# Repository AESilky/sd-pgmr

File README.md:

# Silky Design - Flash ROM Programmer

This is a programmer for the popular SST39SF010A/020A/040 devices from MicroChip.

These devices are 128Mx8, 256Mx8, and 512Mx8, and are used in a number of retro-computing memory and single-board-computers.

The programmer uses a Raspberry Pi Pico2 (RP2350) micro-controller to read image files from a MicroSD card or from the USB port from an application running on a host computer. The RPi Pico2 buffers the image in its internal memory and then writes it to the device.

The programmer can read a Flash device and provides options of saving the device image to the SD card, sending it to a host computer, or writing the image onto another Flash device.

The programmer is powered from the USB port on the RPi Pico2.

The programmer includes a small display and an input knob and switch to navigate through the options, SD card contents, etc.

## Repo Contents

This repo includes:

1. the hardware schematic, PCB layout, and other files needed to produce the PCB.
2. the software for the RPi Pico2, including CMake files to build the RPi Pico2 image.
3. some software for a host computer to communicate with the programmer and transfer files.
4. some component data sheets (for the more unique components)
5. 3D print files for a simple enclosure

## License

Except where noted, the software and hardware for this project is designed/authored by AESilky, and is licensed under the MIT License (included in the repo in the LICENSE file).

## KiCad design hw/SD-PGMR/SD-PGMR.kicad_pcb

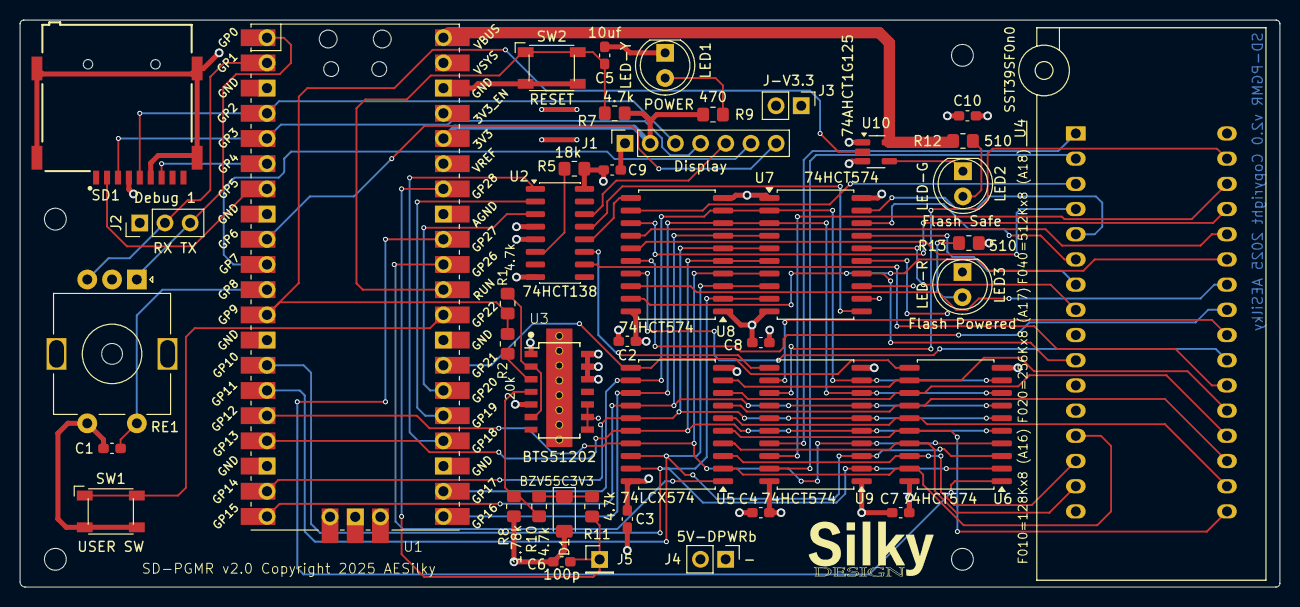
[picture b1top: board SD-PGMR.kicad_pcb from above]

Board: 4 copper layers, 127.0 x 57.1 mm, 48 parts (0 on the bottom side), 75 nets.

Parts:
C1, C2, C3, C4, C7, C8, C9, C10: 0.1uF; C_0603_1608Metric_Pad1.08x0.95mm_HandSolder
C5: 10uf; C_0603_1608Metric_Pad1.08x0.95mm_HandSolder
C6: 100p; C_0603_1608Metric_Pad1.08x0.95mm_HandSolder
D1: BZV55C3V3; D_MiniMELF
G1: LOGO; SILKY-DESIGN-logo-0_50-AES
H1, H2, H3, H4: MountingHole; MountingHole_2.2mm_M2
J1: CONN_01x07 Socket; PinSocket_1x07_P2.54mm_Vertical
J2: Conn_01x03 HDR; PinHeader_1x03_P2.54mm_Vertical
J3: J-V3.3; PinHeader_1x02_P2.54mm_Vertical
J4: CONN 1x2 HDR; PinHeader_1x02_P2.54mm_Vertical
J5: HDR 1x1 Pin; PinHeader_1x01_P2.54mm_Vertical
LED1: LED-Y; LED_D5.0mm
LED2: LED-G; LED_D5.0mm
LED3: LED-R; LED_D5.0mm
R1, R7, R10, R11: 4.7k; R_0805_2012Metric_Pad1.20x1.40mm_HandSolder
R2: 20k; R_0805_2012Metric_Pad1.20x1.40mm_HandSolder
R5: 18k; R_0805_2012Metric_Pad1.20x1.40mm_HandSolder
R8: 1.78k; R_0805_2012Metric_Pad1.20x1.40mm_HandSolder
R9: 470; R_0805_2012Metric_Pad1.20x1.40mm_HandSolder
R12, R13: 510; R_0805_2012Metric_Pad1.20x1.40mm_HandSolder
RE1: RotEnc-SW; RotaryEncoder_Alps_EC11E-Switch_Vertical_H20mm_MountingHoles
SD1: MicroSD-Socket; AES-SDCard-GCT_MEM2075-00-140-01-A
SW1, SW2: SW PB-MOM; AES-SW_PUSH_SMD_1P1T_NO_45x45mm-CK
U1: AES-Pico; AES-RPi_Pico_SMD_TH
U2: 74HCT138; SOIC-16_3.9x9.9mm_P1.27mm
U3: BTS51202; AES-Inf-BTS5120-DSOP14-BP
U4: SST39SF0n0; DIP_Socket-32_W11.9_W12.7_W15.24_W17.78_W18.5_3M_232-1285-0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
U5: 74LCX574; SOIC-20W_7.5x12.8mm_P1.27mm
U6, U7, U8, U9: 74HCT574; SOIC-20W_7.5x12.8mm_P1.27mm
U10: 74AHCT1G125; SOT-23-5_HandSoldering

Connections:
+3.3V: C3.2, J1.2, J3.2, R7.1, R9.1, SD1.4 (VDD), U1.36 (3V3), U5.20 (VCC)
+5DP: C2.2, C4.2, C7.2, C8.2, C9.2, C10.2, R5.2, R13.2, U2.16 (VCC), U3.12 (OUT0a), U3.13 (OUT0b), U3.14 (OUT0c), U4.32 (VCC), U6.20 (VCC), U7.20 (VCC), U8.20 (VCC), U9.20 (VCC)
+5V: R12.1, U1.39 (VSYS), U1.40 (VBUS), U3.CT (VS), U10.5 (VCC)
/A0: U1.24 (GPIO18), U2.1 (A0)
/A1: U1.25 (GPIO19), U2.2 (A1)
/A2: U1.26 (GPIO20), U2.3 (A2)
/ADH_LD-: U2.11 (O4), U9.11 (Cp)
/ADL_LD-: U2.13 (O2), U7.11 (Cp)
/ADM_LD-: U2.12 (O3), U8.11 (Cp)
/ATTN-: SW1.1, U1.29 (GPIO22)
/BA0: U4.12 (A0), U7.12 (Q7)
/BA1: U4.11 (A1), U7.13 (Q6)
/BA2: U4.10 (A2), U7.14 (Q5)
/BA3: U4.9 (A3), U7.15 (Q4)
/BA4: U4.8 (A4), U7.16 (Q3)
/BA5: U4.7 (A5), U7.17 (Q2)
/BA6: U4.6 (A6), U7.18 (Q1)
/BA7: U4.5 (A7), U7.19 (Q0)
/BA8: U4.27 (A8), U8.19 (Q0)
/BA9: U4.26 (A9), U8.18 (Q1)
/BA10: U4.23 (A10), U8.17 (Q2)
/BA11: U4.25 (A11), U8.16 (Q3)
/BA12: U4.4 (A12), U8.15 (Q4)
/BA13: U4.28 (A13), U8.14 (Q5)
/BA14: U4.29 (A14), U8.13 (Q6)
/BA15: U4.3 (A15), U8.12 (Q7)
/BA16: U4.2 (A16), U9.19 (Q0)
/BA17: U4.30 (A17), U9.18 (Q1)
/BA18: U4.1 (A18), U9.17 (Q2)
/BD0: U4.13 (D0), U5.2 (D0), U6.19 (Q0)
/BD1: U4.14 (D1), U5.3 (D1), U6.18 (Q1)
/BD2: U4.15 (D2), U5.4 (D2), U6.17 (Q2)
/BD3: U4.17 (D3), U5.5 (D3), U6.16 (Q3)
/BD4: U4.18 (D4), U5.6 (D4), U6.15 (Q4)
/BD5: U4.19 (D5), U5.7 (D5), U6.14 (Q5)
/BD6: U4.20 (D6), U5.8 (D6), U6.13 (Q6)
/BD7: U4.21 (D7), U5.9 (D7), U6.12 (Q7)
/CARD_CS-: SD1.2 (DAT3/CD), U1.7 (GPIO5)
/DISPRST-: J1.5, U2.14 (O1)
/DISP_CD: J1.6, U1.10 (GPIO7)
/DISP_CS-: J1.7, U1.9 (GPIO6)
/DLATCH: U1.27 (GPIO21), U5.11 (Cp), U6.11 (Cp)
/DPSENS: C6.2, J5.1, R11.2, U1.34 (GPIO28_ADC2)
/FPWR_ON: R1.1, R2.1, U1.12 (GPIO9), U10.2
/FRD-: U4.24 (OE), U9.12 (Q7)
/FWR-: U4.31 (PGM), U9.13 (Q6)
/F_SEL-: U2.10 (O5), U4.22 (CE)
/PD0: U1.14 (GPIO10), U5.19 (Q0), U6.2 (D0), U7.9 (D7), U8.2 (D0), U9.2 (D0)
/PD1: U1.15 (GPIO11), U5.18 (Q1), U6.3 (D1), U7.8 (D6), U8.3 (D1), U9.3 (D1)
/PD2: U1.16 (GPIO12), U5.17 (Q2), U6.4 (D2), U7.7 (D5), U8.4 (D2), U9.4 (D2)
/PD3: U1.17 (GPIO13), U5.16 (Q3), U6.5 (D3), U7.6 (D4), U8.5 (D3), U9.5 (D3)
/PD4: U1.19 (GPIO14), U5.15 (Q4), U6.6 (D4), U7.5 (D3), U8.6 (D4), U9.6 (D4)
/PD5: U1.20 (GPIO15), U5.14 (Q5), U6.7 (D5), U7.4 (D2), U8.7 (D5), U9.7 (D5)
/PD6: U1.21 (GPIO16), U5.13 (Q6), U6.8 (D6), U7.3 (D1), U8.8 (D6), U9.8 (D6)
/PD7: U1.22 (GPIO17), U5.12 (Q7), U6.9 (D7), U7.2 (D0), U8.9 (D7), U9.9 (D7)
/PRD-: U1.31 (GPIO26_ADC0), U5.1 (OE)
/PWR-: U1.32 (GPIO27_ADC1), U6.1 (OE)
/RESET-: C5.1, R7.2, SW2.1, U1.30 (RUN)
/RE_A: J2.3, RE1.A, U1.1 (GPIO0)
/RE_B: J2.2, RE1.B, U1.2 (GPIO1)
/RE_SW-: C1.1, RE1.S2, U1.11 (GPIO8)
/SPICK: J1.3, SD1.5 (CLK), U1.4 (GPIO2)
/SPIMI: SD1.7 (DAT0), U1.6 (GPIO4)
/SPIMO: J1.4, SD1.3 (CMD), U1.5 (GPIO3)
GND: C1.2, C2.1, C3.1, C4.1, C5.2, C6.1, C7.1, C8.1, C9.1, C10.1, D1.2 (A), J1.1, J2.1, J3.1, J4.1, LED1.1 (K), LED3.1 (K), R8.2, RE1.C, RE1.S1, SD1.6 (VSS), SD1.10 (SHIELD), SW1.2, SW2.2, U1.3 (GND), U1.8 (GND), U1.13 (GND), U1.18 (GND), U1.23 (GND), U1.28 (GND), U1.33 (AGND), U1.38 (GND), U2.4 (E1), U2.5 (E2), U2.8 (GND), U3.1 (GND), U3.5 (DS1), U4.16 (GND), U5.10 (GND), U6.10 (GND), U7.1 (OE), U7.10 (GND), U8.1 (OE), U8.10 (GND), U9.1 (OE), U9.10 (GND), U10.1, U10.3 (GND)
unnamed: D1.1 (K), R10.2, R11.1
unnamed: J4.2, U3.8 (OUT1a), U3.9 (OUT1b), U3.10 (OUT1c)
unnamed: LED1.2 (A), R9.2
unnamed: LED2.2 (A), R12.2
unnamed: LED2.1 (K), U10.4
unnamed: LED3.2 (A), R13.1
unnamed: R5.1, U2.6 (E3)
unnamed: R2.2, U3.3 (DEN)
unnamed: R1.2, U3.2 (IN0), U3.6 (IN1)
unnamed: R8.1, R10.1, U3.4 (IS)

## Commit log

2025-09-23 Initial
2025-09-23 Update gitignore to skip KiCad lock and backup files.
2025-09-26 PCB v1.0 (ordered)
2025-09-28 Initial SW project builds/runs
2025-09-28 Display: Reorganze for easier use of other displays.
2025-09-30 SD support added. Virtual RTC for RP2350.
2025-10-04 PCB: BOM and Assy file created
2025-10-05 Device (Flash) operations.
2025-10-06 Debugging Support: stdio starts on uart, switch to usb.
2025-10-06 HID/APP: Raname HID to APP
2025-10-21 Add command shell to allow operations.
2025-10-24 Shell: added. Device: Corrected signal generation.
2025-10-31 Shell: Change ESC sequence buffer size.
2025-10-31 Shell: Add an error printf.
2025-11-05 PGMR: Last of this PCB. New version needed for device power.
2025-11-25 Re-design and re-layout with new power circuit
2025-11-26 Refactor, compiles and runs
2025-11-28 Flash RD and WR tested.
2025-11-30 Rotary: Fix retrieve value problem. PD: add Power-Mode.
2025-12-01 MenuMgr: First cut functioning. Still needs work.
2025-12-05 ProgDev: Reading type. Checking empty.
2025-12-08 SD: SD/FS using debug_trace. Runon_core0 for disk ops from core1.
2025-12-09 Erase sector and full part.
2025-12-10 Program device from binary image file.
2026-01-06 Programming from file on CLI
2026-01-14 Menus and file select working (verify)
2026-01-14 Programming from rotary
2026-01-16 Terminal interface full function.

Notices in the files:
hw/SD-PGMR/SD-PGMR.kicad_pcb:
Copyright 2025 AESilky
SD-PGMR v2.0 Copyright 2025 AESilky
